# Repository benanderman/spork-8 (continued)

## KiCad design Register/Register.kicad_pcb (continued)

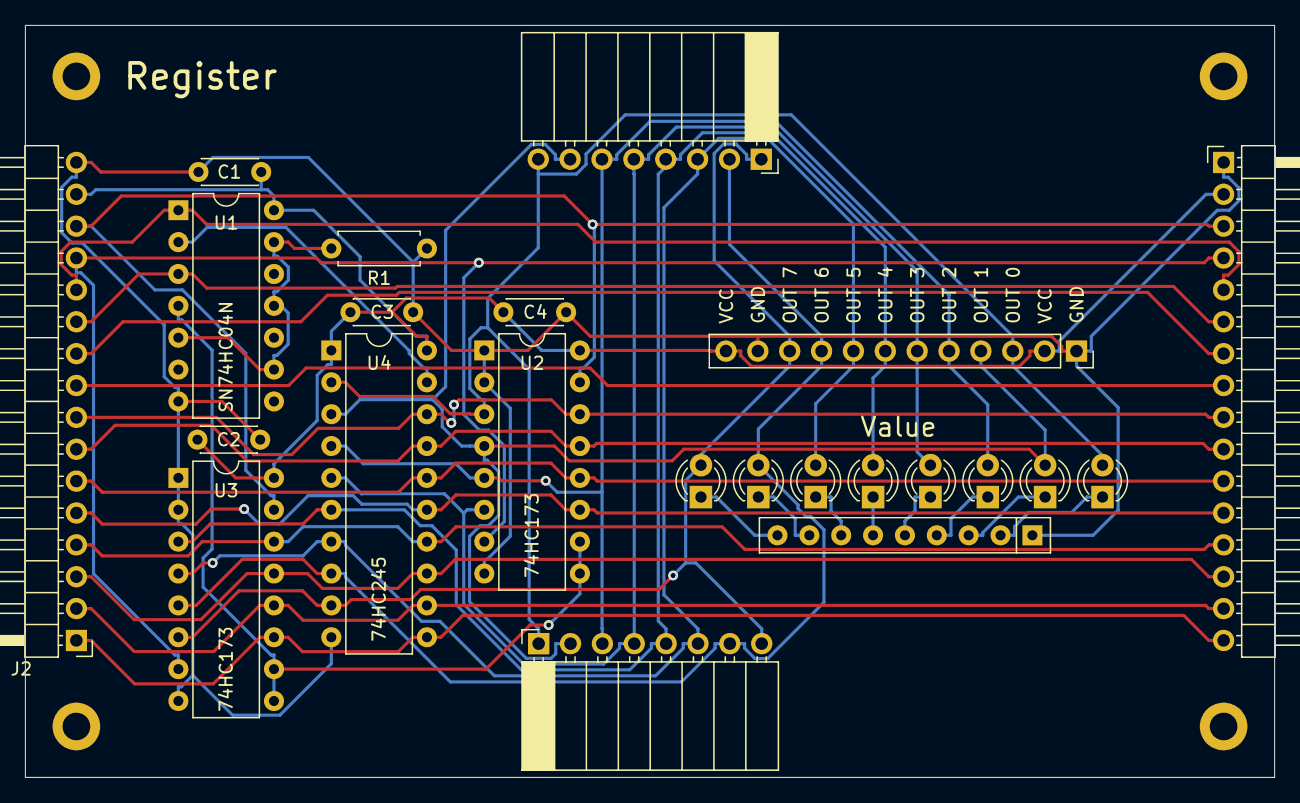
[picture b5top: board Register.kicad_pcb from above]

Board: 2 copper layers, 99.6 x 59.9 mm, 27 parts (0 on the bottom side), 35 nets.

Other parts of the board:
HOLE1, HOLE2, HOLE3, HOLE4: MountingHole_2.2mm_M2_DIN965_Pad

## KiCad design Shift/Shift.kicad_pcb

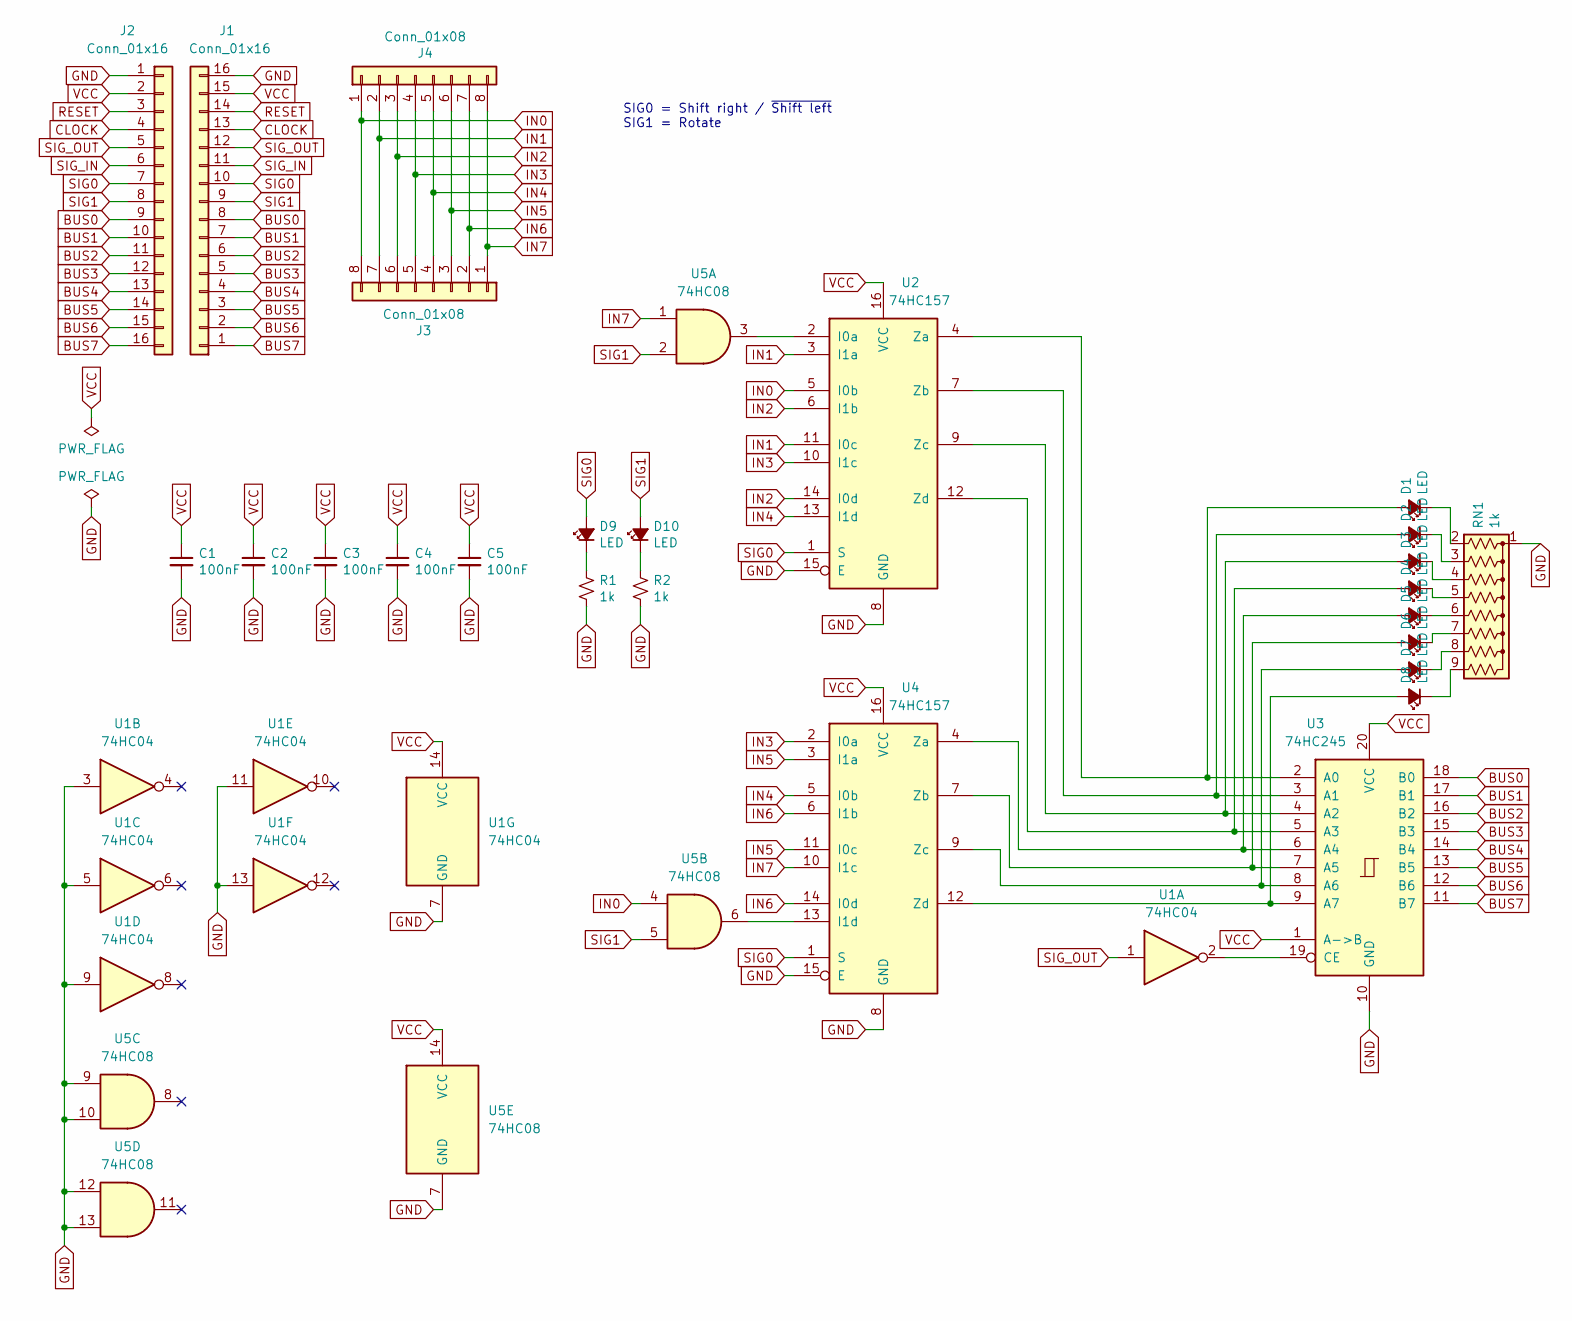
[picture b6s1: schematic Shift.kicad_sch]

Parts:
C1, C2, C3, C4, C5: 100nF; C_Disc_D4.3mm_W1.9mm_P5.00mm
D1, D2, D3, D4, D5, D6, D7, D8, D9, D10: LED; LED_D3.0mm_Clear
J1, J2: Conn_01x16; PinHeader_1x16_P2.54mm_Horizontal
J3, J4: Conn_01x08; PinHeader_1x08_P2.54mm_Horizontal
R1, R2: 1k; R_Axial_DIN0207_L6.3mm_D2.5mm_P7.62mm_Horizontal
RN1: 1k; R_Array_SIP9
U1: 74HC04; DIP-14_W7.62mm
U2, U4: 74HC157; DIP-16_W7.62mm
U3: 74HC245; DIP-20_W7.62mm
U5: 74HC08; DIP-14_W7.62mm

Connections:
BUS0: J1.8, J2.9, U3.18 (B0)
BUS1: J1.7, J2.10, U3.17 (B1)
BUS2: J1.6, J2.11, U3.16 (B2)
BUS3: J1.5, J2.12, U3.15 (B3)
BUS4: J1.4, J2.13, U3.14 (B4)
BUS5: J1.3, J2.14, U3.13 (B5)
BUS6: J1.2, J2.15, U3.12 (B6)
BUS7: J1.1, J2.16, U3.11 (B7)
CLOCK: J1.13, J2.4
GND: C1.2, C2.2, C3.2, C4.2, C5.2, J1.16, J2.1, R1.2, R2.2, RN1.1 (common), U1.3, U1.5, U1.7 (GND), U1.9, U1.11, U1.13, U2.8 (GND), U2.15 (E), U3.10 (GND), U4.8 (GND), U4.15 (E), U5.7 (GND), U5.9, U5.10, U5.12, U5.13
IN0: J3.8, J4.1, U2.5 (I0b), U5.4
IN1: J3.7, J4.2, U2.3 (I1a), U2.11 (I0c)
IN2: J3.6, J4.3, U2.6 (I1b), U2.14 (I0d)
IN3: J3.5, J4.4, U2.10 (I1c), U4.2 (I0a)
IN4: J3.4, J4.5, U2.13 (I1d), U4.5 (I0b)
IN5: J3.3, J4.6, U4.3 (I1a), U4.11 (I0c)
IN6: J3.2, J4.7, U4.6 (I1b), U4.14 (I0d)
IN7: J3.1, J4.8, U4.10 (I1c), U5.1
unnamed: D1.2 (A), U2.4 (Za), U3.2 (A0)
unnamed: D1.1 (K), RN1.2 (R1)
unnamed: D2.2 (A), U2.7 (Zb), U3.3 (A1)
unnamed: D2.1 (K), RN1.3 (R2)
unnamed: D3.2 (A), U2.9 (Zc), U3.4 (A2)
unnamed: D3.1 (K), RN1.4 (R3)
unnamed: D4.2 (A), U2.12 (Zd), U3.5 (A3)
unnamed: D4.1 (K), RN1.5 (R4)
unnamed: D5.2 (A), U3.6 (A4), U4.4 (Za)
unnamed: D5.1 (K), RN1.6 (R5)
unnamed: D6.2 (A), U3.7 (A5), U4.7 (Zb)
unnamed: D6.1 (K), RN1.7 (R6)
unnamed: D7.2 (A), U3.8 (A6), U4.9 (Zc)
unnamed: D7.1 (K), RN1.8 (R7)
unnamed: D8.2 (A), U3.9 (A7), U4.12 (Zd)
unnamed: D8.1 (K), RN1.9 (R8)
unnamed: D9.1 (K), R1.1
unnamed: D10.1 (K), R2.1
unnamed: U2.2 (I0a), U5.3
unnamed: U1.2, U3.19 (CE)
unnamed: U4.13 (I1d), U5.6
RESET: J1.14, J2.3
SIG0: D9.2 (A), J1.10, J2.7, U2.1 (S), U4.1 (S)
SIG1: D10.2 (A), J1.9, J2.8, U5.2, U5.5
SIG_IN: J1.11, J2.6
SIG_OUT: J1.12, J2.5, U1.1
VCC: C1.1, C2.1, C3.1, C4.1, C5.1, J1.15, J2.2, U1.14 (VCC), U2.16 (VCC), U3.1 (A->B), U3.20 (VCC), U4.16 (VCC), U5.14 (VCC)

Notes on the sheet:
SIG0 = Shift right / ~{Shift left} SIG1 = Rotate

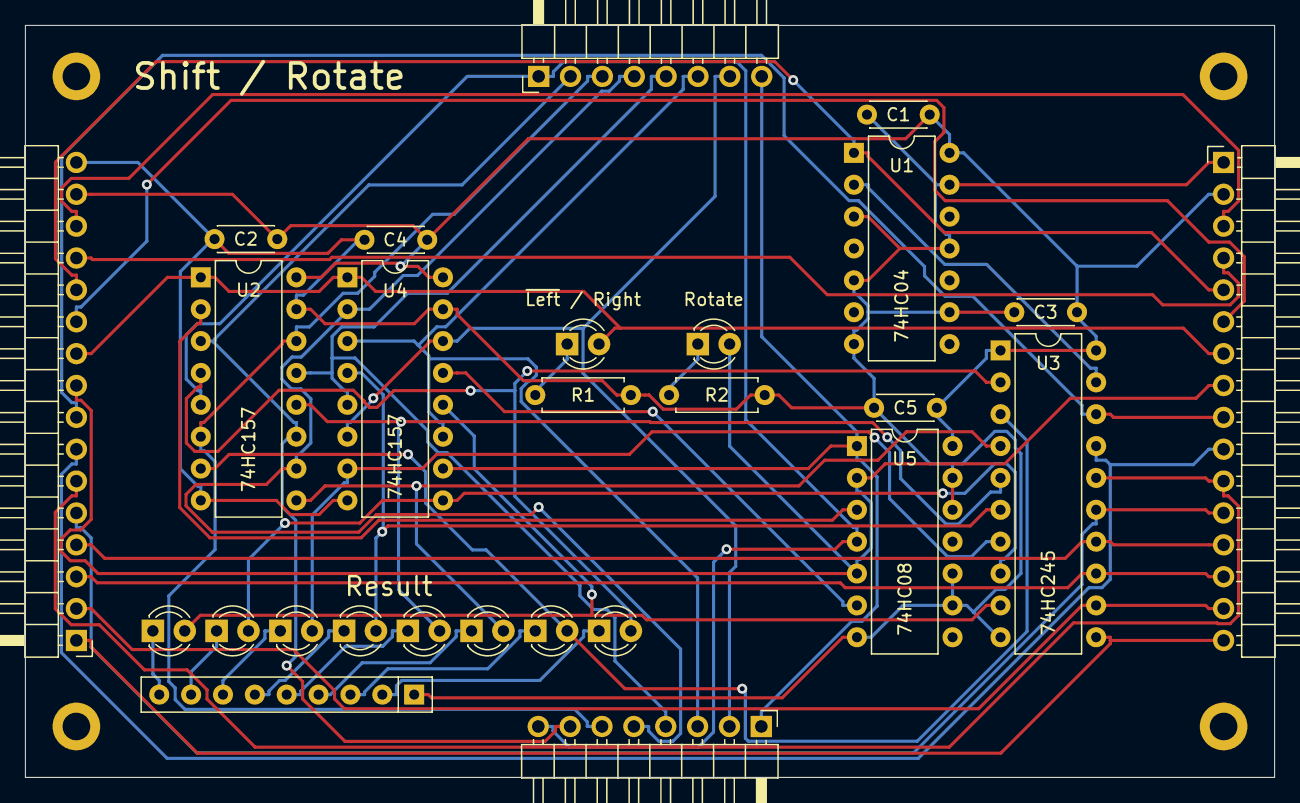
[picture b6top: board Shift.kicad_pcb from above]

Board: 2 copper layers, 99.6 x 59.9 mm, 31 parts (0 on the bottom side), 45 nets.

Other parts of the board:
HOLE1, HOLE2, HOLE3, HOLE4: MountingHole_2.2mm_M2_DIN965_Pad
